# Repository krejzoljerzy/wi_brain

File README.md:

wi_brain
========

Wifi interface board for rc purpose
test

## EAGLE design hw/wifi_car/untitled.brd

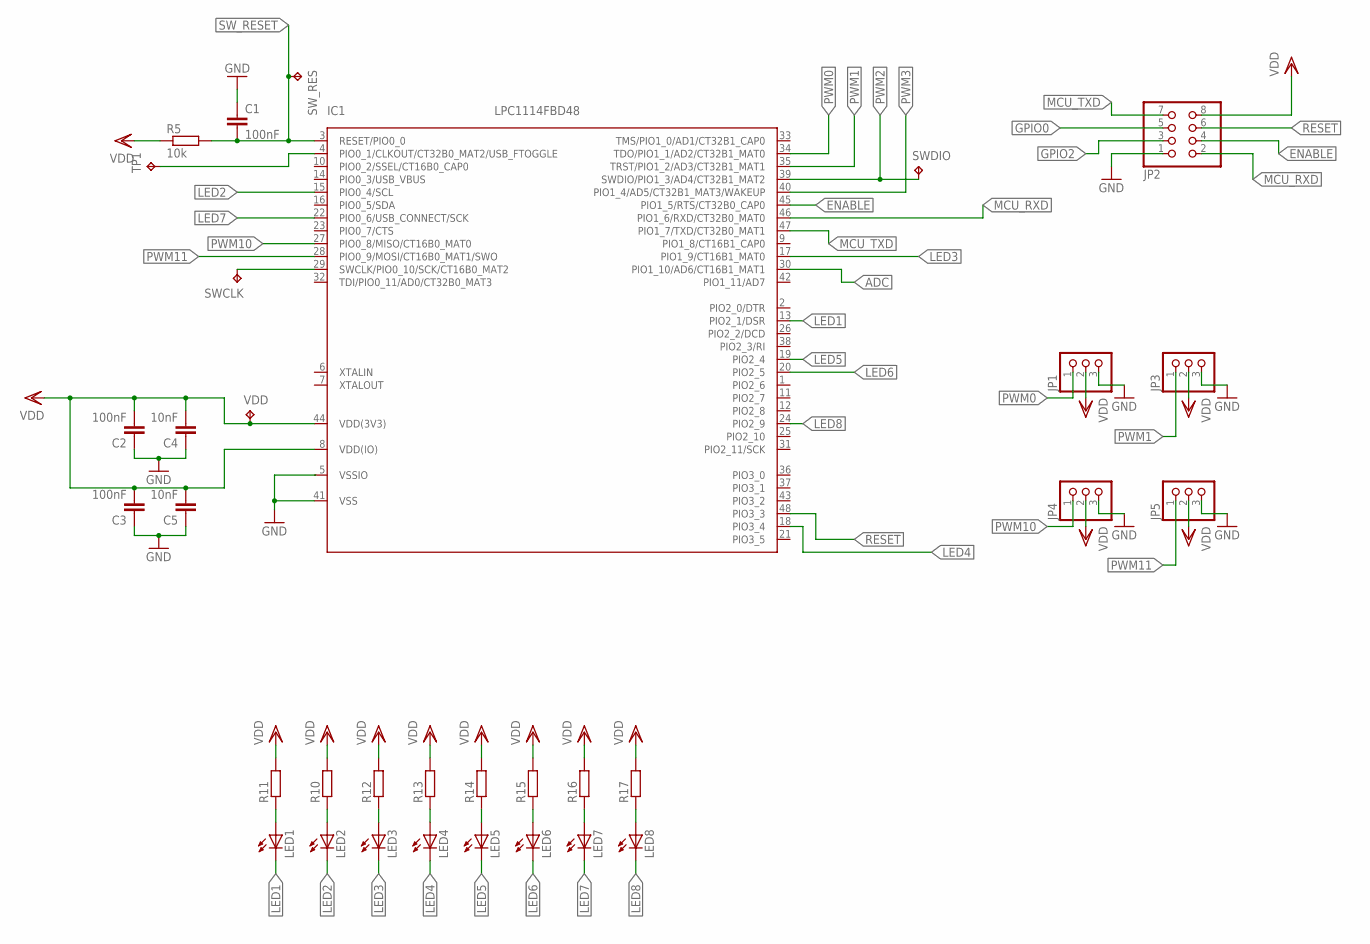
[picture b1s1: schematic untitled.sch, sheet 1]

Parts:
C1, C2, C3: 100nF; C0805
C4, C5: 10nF; C0805
IC1: LPC1114FBD48; LQFP48-7X7
JP1, JP3, JP4, JP5: PINHD-1X3; 1X03
JP2: PINHD-2X4; 2X04
LED1, LED2, LED3, LED4, LED5, LED6, LED7, LED8: LEDCHIP-LED0805; CHIP-LED0805
R5: 10k; R0805
R10, R11, R12, R13, R14, R15, R16, R17: R-EU_R0805; R0805
SWCLK: TPB1,27; B1,27
SWDIO: TPB1,27; B1,27
SW_RES: TPB1,27; B1,27
TP1: TPB1,27; B1,27
VDD: TPB1,27; B1,27

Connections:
ADC: IC1.30 (PIO1_10/AD6/CT16B1_MAT1); also elsewhere on the board
ENABLE: IC1.45 (PIO1_5/RTS/CT32B0_CAP0), JP2.4
GND: C1.1, C2.1, C3.1, C4.1, C5.1, IC1.41 (VSS), JP1.3, JP2.1, JP3.3, JP4.3, JP5.3; also elsewhere on the board
GPIO0: JP2.5
GPIO2: JP2.3
LED1: IC1.13 (PIO2_1/DSR), LED1.C
LED2: IC1.15 (PIO0_4/SCL), LED2.C
LED3: IC1.17 (PIO1_9/CT16B1_MAT0), LED3.C
LED4: IC1.18 (PIO3_4), LED4.C
LED5: IC1.19 (PIO2_4), LED5.C
LED6: IC1.20 (PIO2_5), LED6.C
LED7: IC1.22 (PIO0_6/USB_CONNECT/SCK), LED7.C
LED8: IC1.24 (PIO2_9), LED8.C
MCU_RXD: IC1.46 (PIO1_6/RXD/CT32B0_MAT0), JP2.2
MCU_TXD: IC1.47 (PIO1_7/TXD/CT32B0_MAT1), JP2.7
unnamed: LED1.A, R11.1
unnamed: LED2.A, R10.1
unnamed: LED3.A, R12.1
unnamed: LED4.A, R13.1
unnamed: LED5.A, R14.1
unnamed: LED6.A, R15.1
unnamed: LED7.A, R16.1
unnamed: LED8.A, R17.1
unnamed: IC1.4 (PIO0_1/CLKOUT/CT32B0_MAT2/USB_FTOGGLE), TP1.TP
PWM0: IC1.34 (TDO/PIO1_1/AD2/CT32B1_MAT0), JP1.1
PWM1: IC1.35 (TRST/PIO1_2/AD3/CT32B1_MAT1), JP3.1
PWM2: IC1.39 (SWDIO/PIO1_3/AD4/CT32B1_MAT2), SWDIO.TP; also elsewhere on the board
PWM3: IC1.40 (PIO1_4/AD5/CT32B1_MAT3/WAKEUP); also elsewhere on the board
PWM10: IC1.27 (PIO0_8/MISO/CT16B0_MAT0), JP4.1
PWM11: IC1.28 (PIO0_9/MOSI/CT16B0_MAT1/SWO), JP5.1
PWM12: IC1.29 (SWCLK/PIO0_10/SCK/CT16B0_MAT2), SWCLK.TP
RESET: IC1.48 (PIO3_3), JP2.6
SW_RESET: C1.2, IC1.3 (RESET/PIO0_0), R5.2, SW_RES.TP
VDD: C2.2, C3.2, C4.2, C5.2, IC1.8 (VDD(IO)), IC1.44 (VDD(3V3)), JP1.2, JP2.8, JP3.2, JP4.2, JP5.2, R5.1, R10.2, R11.2, R12.2, R13.2, R14.2, R15.2, R16.2, R17.2, VDD.TP; also elsewhere on the board
VSSIO: IC1.5 (VSSIO)

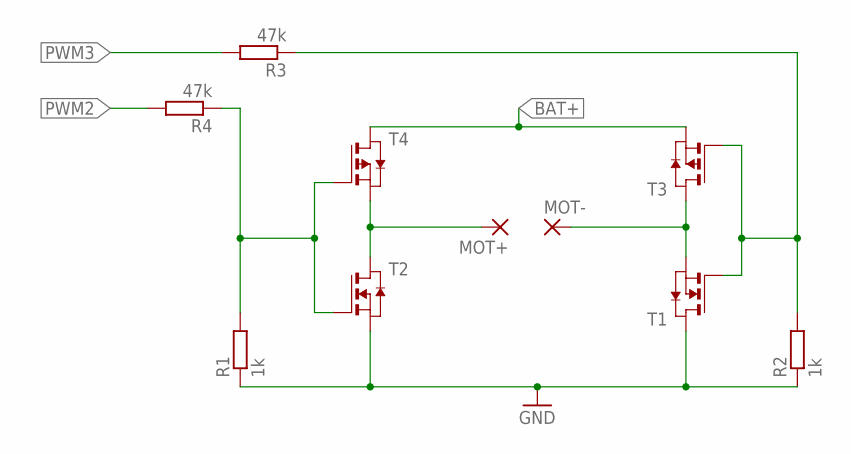
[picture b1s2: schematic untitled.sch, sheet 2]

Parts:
MOT+: SMD5; SMD2,54-5,08
MOT-: SMD5; SMD2,54-5,08
R1, R2: 1k; R0805
R3, R4: 47k; R0805
T1, T2: NMOSSOT23; SOT-23
T3, T4: PMOSSOT23; SOT-23

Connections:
BAT+: T3.2 (S), T4.1 (D); also elsewhere on the board
GND: R1.1, R2.1, T1.1 (D), T2.2 (S); also elsewhere on the board
unnamed: R2.2, R3.1, T1.3 (G), T3.3 (G)
unnamed: MOT+.1, T2.1 (D), T4.2 (S)
unnamed: MOT-.1, T1.2 (S), T3.1 (D)
unnamed: R1.2, R4.1, T2.3 (G), T4.3 (G)
PWM2: R4.2; also elsewhere on the board
PWM3: R3.2; also elsewhere on the board

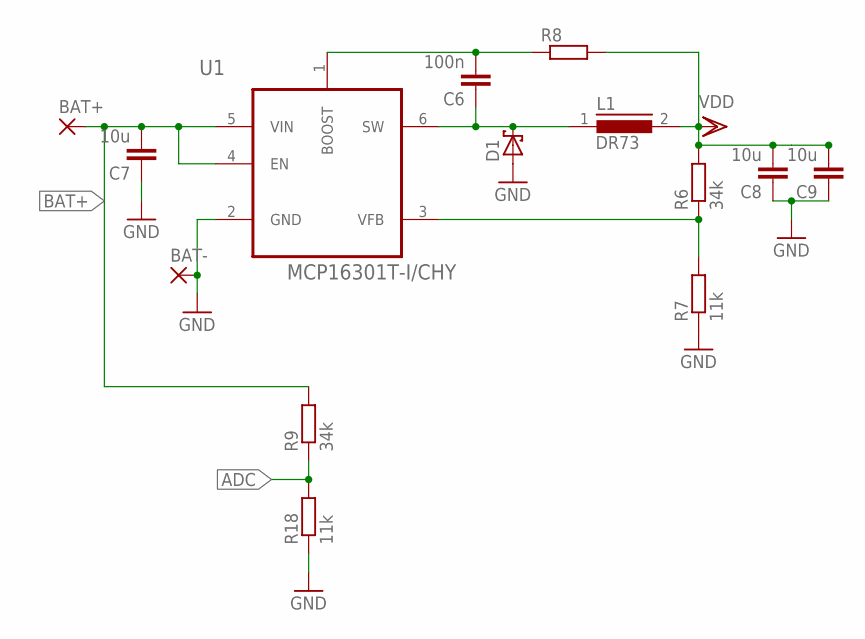
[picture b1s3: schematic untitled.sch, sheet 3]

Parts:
BAT+: SMD5; SMD2,54-5,08
BAT-: SMD5; SMD2,54-5,08
C6: 100n; C0805
C7, C8, C9: 10u; C0805
D1: SCHOTTKY-DIODESMD; SMB
L1: DR73
R6, R9: 34k; R0805
R7, R18: 11k; R0805
R8: R-EU_R0603; R0603
U1: MCP16301T-I/CHY; SOT95P290X145-6N

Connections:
ADC: R9.1, R18.2; also elsewhere on the board
BAT+: BAT+.1, C7.2, R9.2, U1.4 (EN), U1.5 (VIN); also elsewhere on the board
GND: BAT-.1, C7.1, C8.1, C9.1, D1.A, R7.1, R18.1, U1.2 (GND); also elsewhere on the board
unnamed: R6.1, R7.2, U1.3 (VFB)
unnamed: C6.1, D1.C, L1.1, U1.6 (SW)
unnamed: C6.2, R8.1, U1.1 (BOOST)
VDD: C8.2, C9.2, L1.2, R6.2, R8.2; also elsewhere on the board

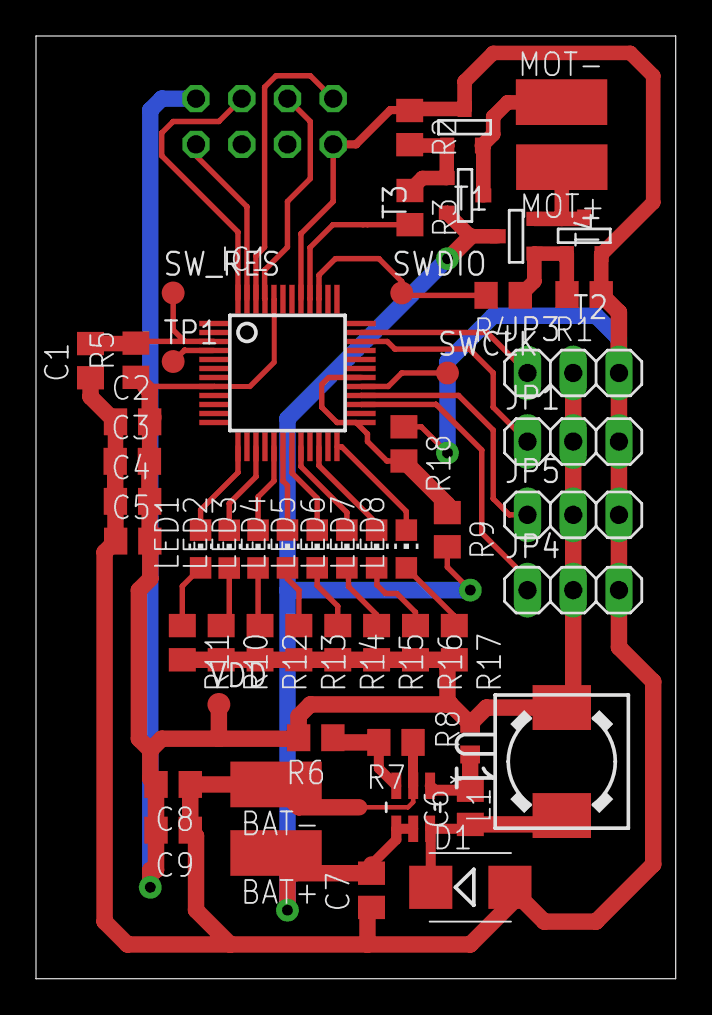
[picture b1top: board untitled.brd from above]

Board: 2 copper layers, 35.5 x 52.4 mm, 57 parts (1 on the bottom side), 40 nets.

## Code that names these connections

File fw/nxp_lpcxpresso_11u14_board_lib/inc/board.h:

/*
 * @brief LPCXpresso 11U14 board file
 *
 * @note
 * Copyright(C) NXP Semiconductors, 2012
 * All rights reserved.
 *
 * @par
 * Software that is described herein is for illustrative purposes only
 * which provides customers with programming information regarding the
 * LPC products.  This software is supplied "AS IS" without any warranties of
 * any kind, and NXP Semiconductors and its licensor disclaim any and
 * all warranties, express or implied, including all implied warranties of
 * merchantability, fitness for a particular purpose and non-infringement of
 * intellectual property rights.  NXP Semiconductors assumes no responsibility
 * or liability for the use of the software, conveys no license or rights under any
 * patent, copyright, mask work right, or any other intellectual property rights in
 * or to any products. NXP Semiconductors reserves the right to make changes
 * in the software without notification. NXP Semiconductors also makes no
 * representation or warranty that such application will be suitable for the
 * specified use without further testing or modification.
 *
 * @par
 * Permission to use, copy, modify, and distribute this software and its
 * documentation is hereby granted, under NXP Semiconductors' and its
 * licensor's relevant copyrights in the software, without fee, provided that it
 * is used in conjunction with NXP Semiconductors microcontrollers.  This
 * copyright, permission, and disclaimer notice must appear in all copies of
 * this code.
 */

#ifndef __BOARD_H_
#define __BOARD_H_

#include "chip.h"
/* board_api.h is included at the bottom of this file after DEBUG setup */

#ifdef __cplusplus
extern "C" {
#endif

/** @defgroup BOARD_NXP_XPRESSO_11U14 NXP LPC11U14 LPCXpresso board support software API functions
 * @ingroup LPCOPEN_11XX_BOARD_XPRESSO_11U14
 * The board support software API functions provide some simple abstracted
 * functions used across multiple LPCOpen board examples. See @ref BOARD_COMMON_API
 * for the functions defined by this board support layer.<br>
 * @{
 */

/** @defgroup BOARD_NXP_XPRESSO_11U14_OPTIONS BOARD: NXP LPC11U14 LPCXpresso board build options
 * This board has options that configure its operation at build-time.<br>
 * @{
 */

/** Define DEBUG_ENABLE to enable IO via the DEBUGSTR, DEBUGOUT, and
    DEBUGIN macros. If not defined, DEBUG* functions will be optimized
	out of the code at build time.
 */
//#define DEBUG_ENABLE

/** Define DEBUG_SEMIHOSTING along with DEBUG_ENABLE to enable IO support
    via semihosting. You may need to use a C library that supports
	semihosting with this option.
 */
//#define DEBUG_SEMIHOSTING

/** Board UART used for debug output and input using the DEBUG* macros. This
    is also the port used for Board_UARTPutChar, Board_UARTGetChar, and
	Board_UARTPutSTR functions.
 */
#define DEBUG_UART LPC_USART

/**
 * @}
 */

/* Board name */
#define BOARD_NXP_XPRESSO_11U14

/**
 * LED defines
 */
#define LEDS_LED1           0x01
#define LEDS_LED2           0x02
#define LEDS_LED3           0x04
#define LEDS_LED4           0x08
#define LEDS_LED5           0x10
#define LEDS_LED6           0x20
#define LEDS_LED7           0x40
#define LEDS_LED8           0x80
#define LEDS_NO_LEDS        0x00

/**
 *  GPIO defines
 *  WARNING! Pin reserved due to ADC
 *  pin escape routine
 */

#define GPIO_RESERVED_PIN 10
#define GPIO_RESERVED_PORT 2
#define GPIO_LED1_PORT		2
#define GPIO_LED1_PIN		1
#define GPIO_LED2_PORT		0
#define GPIO_LED2_PIN		4
#define GPIO_LED3_PORT		1
#define GPIO_LED3_PIN		9
#define GPIO_LED4_PORT		3
#define GPIO_LED4_PIN		4
#define GPIO_LED5_PORT		2
#define GPIO_LED5_PIN		4
#define GPIO_LED6_PORT		2
#define GPIO_LED6_PIN		5
#define GPIO_LED7_PORT		0
#define GPIO_LED7_PIN		6
#define GPIO_LED8_PORT		2
#define GPIO_LED8_PIN		9

 /**
  * Battery measurement ADC pins
  */
#define ADC_PORT 1
#define ADC_PIN 10

/**
 *  General use PWM outputs
 */
#define PWM_0_PORT	1
#define PWM_0_PIN	1
#define PWM_1_PORT	1
#define PWM_1_PIN	2
#define PWM_10_PORT 0
#define PWM_10_PIN	8
#define PWM_11_PORT	0
#define PWM_11_PIN	9

/**
 *  PWM used for H bridge driving
 */
#define MOTORA_PORT	1
#define MOTORA_PIN	3
#define MOTORB_PORT	1
#define MOTORB_PIN	4

/**
 * UART defines
 */
#define UART_BAUDRATE		9600
/**
 * @brief	Initialize buttons on the board
 * @return	Nothing
 */
void Board_Buttons_Init(void);

/**
 * @brief	Get button status
 * @return	status of button
 */
uint32_t Buttons_GetStatus(void);

/**
 * @brief	Initialize Joystick
 * @return	Nothing
 */
void Board_Joystick_Init(void);

/**
 * @brief	Get Joystick status
 * @return	status of Joystick
 */
uint8_t Joystick_GetStatus(void);

/**
 * @}
 */

#include "board_api.h"

#ifdef __cplusplus
}
#endif

#endif /* __BOARD_H_ */

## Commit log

2014-12-27 Git ignore and hardware board files
2014-12-27 Added ADC for battery measurements
2014-12-27 C project created (LPCOpen) and git ignore file update
2014-12-27 Project update on board peripherals
2014-12-27 Board and schematic update
2014-12-27 Git ignore for hw files
